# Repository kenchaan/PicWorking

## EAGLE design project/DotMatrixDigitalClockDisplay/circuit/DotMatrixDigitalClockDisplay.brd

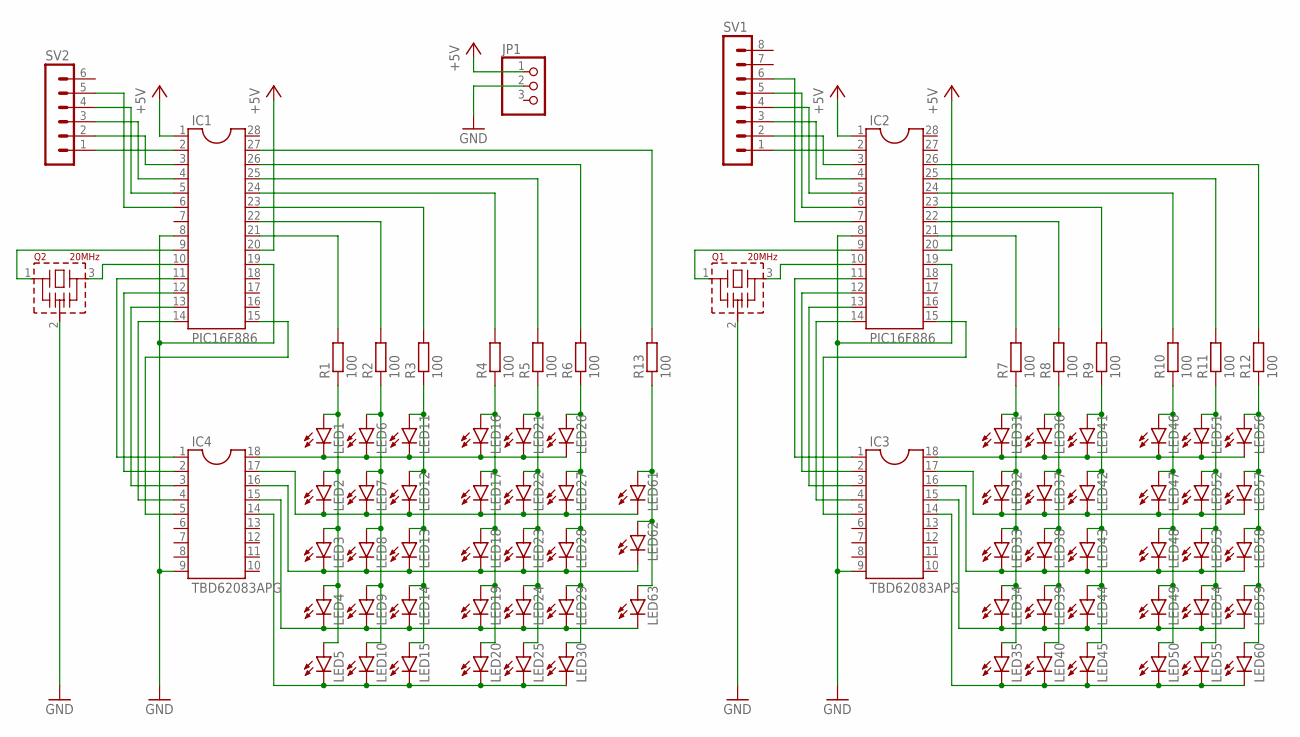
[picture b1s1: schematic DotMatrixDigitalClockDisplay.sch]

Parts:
IC1, IC2: PIC16F886; DIL28-3
IC3, IC4: TBD62083APG; DIL18
JP1: PINHD-1X3; 1X03
LED1, LED2, LED3, LED4, LED5, LED6, LED7, LED8, LED9, LED10, LED11, LED12, LED13, LED14, LED15, LED16, LED17, LED18, LED19, LED20, LED21, LED22, LED23, LED24, LED25, LED26, LED27, LED28, LED29, LED30, LED31, LED32, LED33, LED34, LED35, LED36, LED37, LED38, LED39, LED40, LED41, LED42, LED43, LED44, LED45, LED46, LED47, LED48, LED49, LED50, LED51, LED52, LED53, LED54, LED55, LED56, LED57, LED58, LED59, LED60, LED61, LED62, LED63: LED5MM
Q1, Q2: 20MHz; CSTLS_X
R1, R2, R3, R4, R5, R6, R7, R8, R9, R10, R11, R12, R13: 100; 0207/7
SV1: MA08-1
SV2: MA06-1

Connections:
+5V: IC1.1, IC1.20, IC2.1, IC2.20, JP1.1
GND: IC1.8, IC1.19, IC2.8, IC2.19, IC3.9, IC4.9, JP1.2, Q1.2 (VSS), Q2.2 (VSS)
unnamed: LED1.A, LED2.A, LED3.A, LED4.A, LED5.A, R1.1
unnamed: LED6.A, LED7.A, LED8.A, LED9.A, LED10.A, R2.1
unnamed: LED11.A, LED12.A, LED13.A, LED14.A, LED15.A, R3.1
unnamed: LED16.A, LED17.A, LED18.A, LED19.A, LED20.A, R4.1
unnamed: LED21.A, LED22.A, LED23.A, LED24.A, LED25.A, R5.1
unnamed: LED26.A, LED27.A, LED28.A, LED29.A, LED30.A, R6.1
unnamed: LED31.A, LED32.A, LED33.A, LED34.A, LED35.A, R7.1
unnamed: LED36.A, LED37.A, LED38.A, LED39.A, LED40.A, R8.1
unnamed: LED41.A, LED42.A, LED43.A, LED44.A, LED45.A, R9.1
unnamed: LED46.A, LED47.A, LED48.A, LED49.A, LED50.A, R10.1
unnamed: LED51.A, LED52.A, LED53.A, LED54.A, LED55.A, R11.1
unnamed: LED56.A, LED57.A, LED58.A, LED59.A, LED60.A, R12.1
unnamed: LED61.A, LED62.A, LED63.A, R13.1
unnamed: IC4.18, LED1.K (C), LED6.K (C), LED11.K (C), LED16.K (C), LED21.K (C), LED26.K (C)
unnamed: IC4.17, LED2.K (C), LED7.K (C), LED12.K (C), LED17.K (C), LED22.K (C), LED27.K (C), LED61.K (C)
unnamed: IC4.16, LED3.K (C), LED8.K (C), LED13.K (C), LED18.K (C), LED23.K (C), LED28.K (C), LED62.K (C)
unnamed: IC4.15, LED4.K (C), LED9.K (C), LED14.K (C), LED19.K (C), LED24.K (C), LED29.K (C), LED63.K (C)
unnamed: IC4.14, LED5.K (C), LED10.K (C), LED15.K (C), LED20.K (C), LED25.K (C), LED30.K (C)
unnamed: IC3.18, LED31.K (C), LED36.K (C), LED41.K (C), LED46.K (C), LED51.K (C), LED56.K (C)
unnamed: IC3.17, LED32.K (C), LED37.K (C), LED42.K (C), LED47.K (C), LED52.K (C), LED57.K (C)
unnamed: IC3.16, LED33.K (C), LED38.K (C), LED43.K (C), LED48.K (C), LED53.K (C), LED58.K (C)
unnamed: IC3.15, LED34.K (C), LED39.K (C), LED44.K (C), LED49.K (C), LED54.K (C), LED59.K (C)
unnamed: IC3.14, LED35.K (C), LED40.K (C), LED45.K (C), LED50.K (C), LED55.K (C), LED60.K (C)
unnamed: IC2.14, IC3.4
unnamed: IC2.13, IC3.3
unnamed: IC2.12, IC3.2
unnamed: IC2.11, IC3.1
unnamed: IC2.9, Q1.1
unnamed: IC2.21, R7.2
unnamed: IC2.22, R8.2
unnamed: IC2.23, R9.2
unnamed: IC2.24, R10.2
unnamed: IC2.25, R11.2
unnamed: IC2.26, R12.2
unnamed: IC2.10, Q1.3
unnamed: IC2.15, IC3.5
unnamed: IC1.14, IC4.4
unnamed: IC1.15, IC4.5
unnamed: IC1.13, IC4.3
unnamed: IC1.12, IC4.2
unnamed: IC1.11, IC4.1
unnamed: IC1.21, R1.2
unnamed: IC1.22, R2.2
unnamed: IC1.23, R3.2
unnamed: IC1.24, R4.2
unnamed: IC1.25, R5.2
unnamed: IC1.26, R6.2
unnamed: IC1.27, R13.2
unnamed: IC1.10, Q2.3
unnamed: IC1.9, Q2.1
unnamed: IC1.2, SV2.1
unnamed: IC1.3, SV2.2
unnamed: IC1.4, SV2.3
unnamed: IC1.5, SV2.4
unnamed: IC1.6, SV2.5
unnamed: IC2.2, SV1.1
unnamed: IC2.3, SV1.2
unnamed: IC2.4, SV1.3
unnamed: IC2.5, SV1.4
unnamed: IC2.6, SV1.5
unnamed: IC2.7, SV1.6

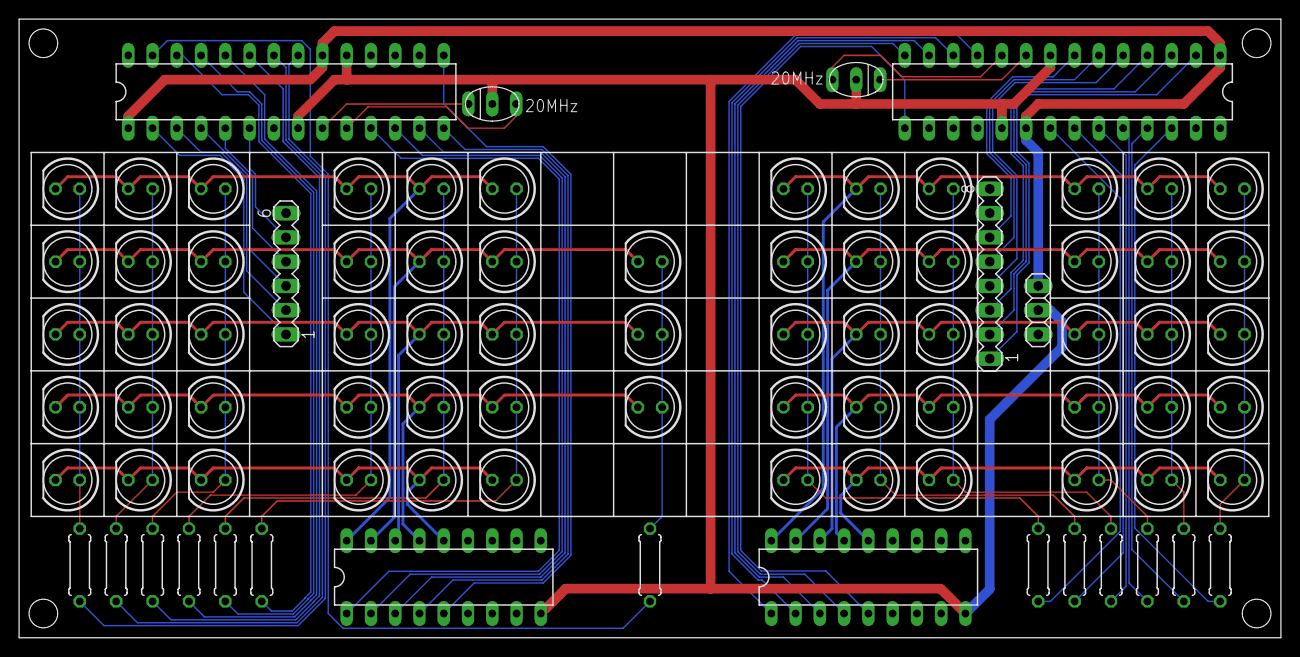
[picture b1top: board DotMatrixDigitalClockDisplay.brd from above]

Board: 2 copper layers, 132.1 x 64.8 mm, 85 parts (0 on the bottom side), 63 nets.

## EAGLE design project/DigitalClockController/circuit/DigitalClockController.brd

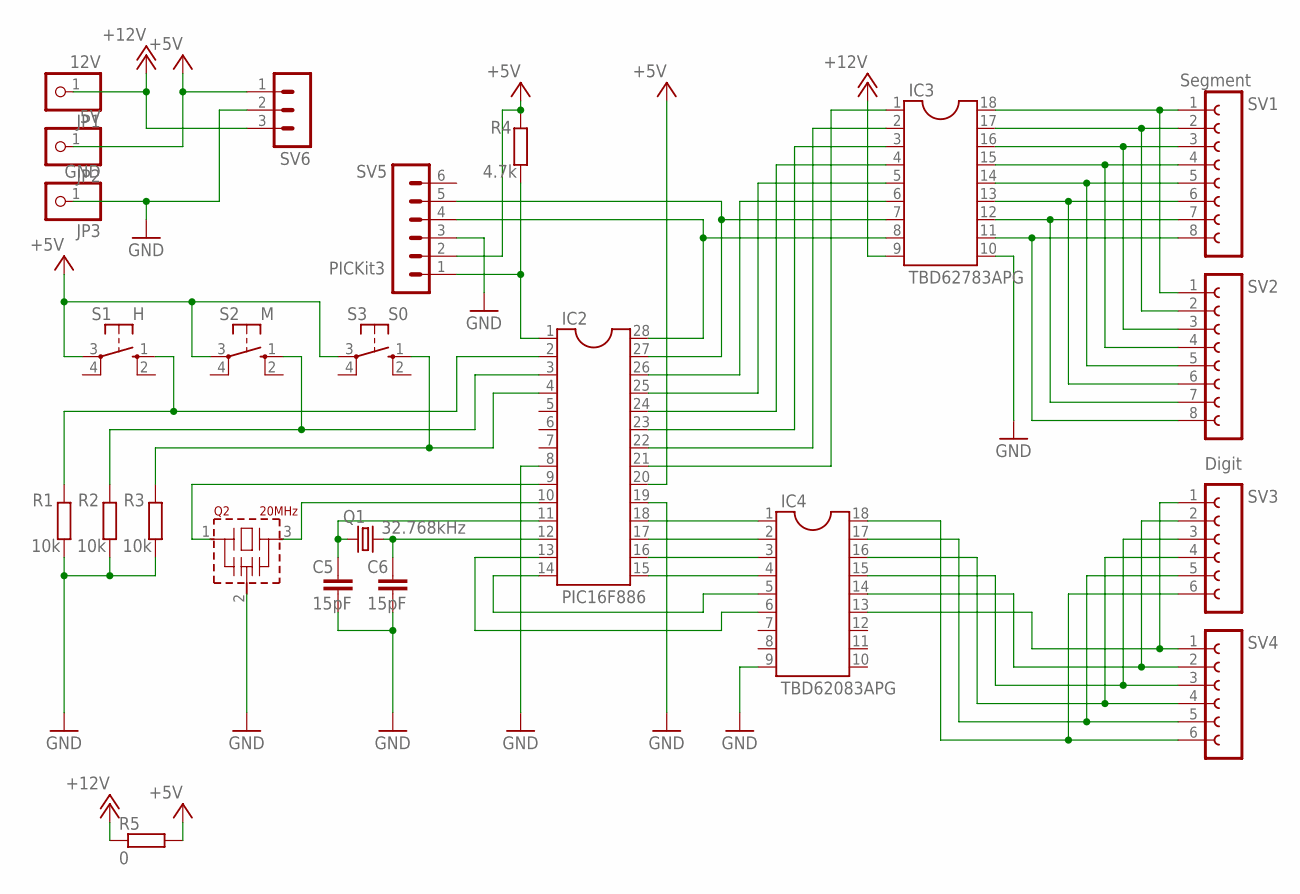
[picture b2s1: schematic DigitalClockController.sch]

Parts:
C5, C6: 15pF; C025-024X044
IC2: PIC16F886; DIL28-3
IC3: TBD62783APG; DIL18
IC4: TBD62083APG; DIL18
JP1: 12V; 1X01
JP2: 5V; 1X01
JP3: GND; 1X01
Q1: 32.768kHz; TC26H
Q2: 20MHz; CSTLS_X
R1, R2, R3: 10k; 0207/10
R4: 4.7k; 0207/10
R5: 0; 0207/10
S1: H; B3F-10XX
S2: M; B3F-10XX
S3: S0; B3F-10XX
SV1, SV2: Segment; FE08
SV3, SV4: Digit; FE06
SV5: PICKit3; MA06-1
SV6: MA03-1

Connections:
+5V: IC2.20, JP2.1, R4.2, R5.2, S1.3, S2.3, S3.3, SV5.2, SV6.1
+12V: IC3.9, JP1.1, R5.1, SV6.3
GND: C5.2, C6.2, IC2.8, IC2.19, IC3.10, IC4.9, JP3.1, Q2.2 (VSS), R1.1, R2.1, R3.1, SV5.3, SV6.2
unnamed: C5.1, IC2.11, Q1.2
unnamed: C6.1, IC2.12, Q1.1
unnamed: IC2.10, Q2.3
unnamed: IC2.9, Q2.1
unnamed: IC2.2, R1.2, S1.1 (S)
unnamed: IC2.3, R2.2, S2.1 (S)
unnamed: IC2.4, R3.2, S3.1 (S)
unnamed: IC2.1, R4.1, SV5.1
unnamed: IC3.18, SV1.1, SV2.1
unnamed: IC3.17, SV1.2, SV2.2
unnamed: IC3.16, SV1.3, SV2.3
unnamed: IC3.15, SV1.4, SV2.4
unnamed: IC2.26, IC3.6
unnamed: IC2.27, IC3.7, SV5.5
unnamed: IC2.25, IC3.5
unnamed: IC2.14, IC4.5
unnamed: IC2.13, IC4.6
unnamed: IC2.15, IC4.4
unnamed: IC2.18, IC4.1
unnamed: IC2.17, IC4.2
unnamed: IC2.16, IC4.3
unnamed: IC2.24, IC3.4
unnamed: IC2.23, IC3.3
unnamed: IC2.22, IC3.2
unnamed: IC2.21, IC3.1
unnamed: IC3.14, SV1.5, SV2.5
unnamed: IC3.13, SV1.6, SV2.6
unnamed: IC3.12, SV1.7, SV2.7
unnamed: IC3.11, SV1.8, SV2.8
unnamed: IC4.13, SV3.1, SV4.1
unnamed: IC4.14, SV3.2, SV4.2
unnamed: IC4.15, SV3.3, SV4.3
unnamed: IC4.16, SV3.4, SV4.4
unnamed: IC4.17, SV3.5, SV4.5
unnamed: IC4.18, SV3.6, SV4.6
unnamed: IC2.28, IC3.8, SV5.4

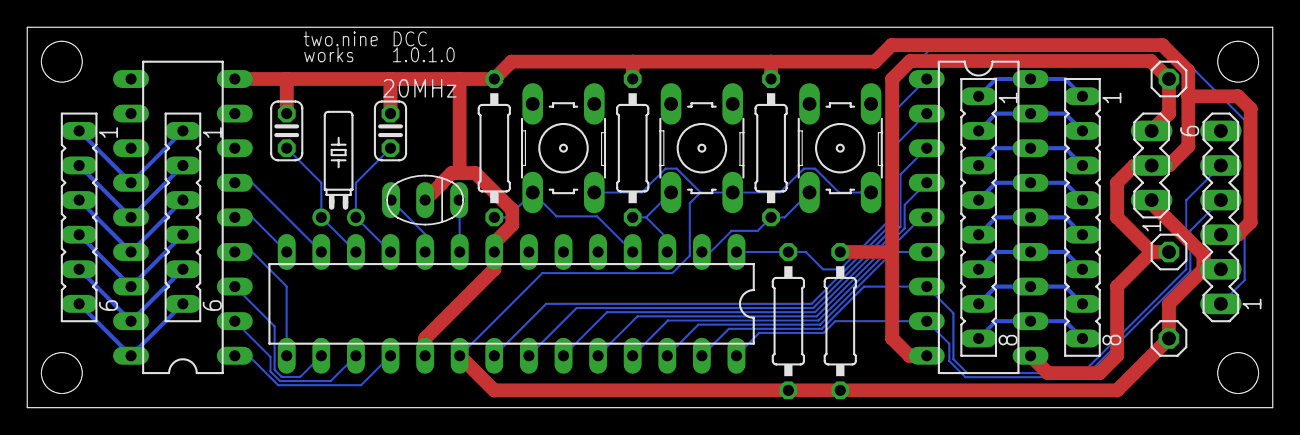
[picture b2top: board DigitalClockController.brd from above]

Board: 2 copper layers, 91.4 x 27.9 mm, 24 parts (0 on the bottom side), 39 nets.

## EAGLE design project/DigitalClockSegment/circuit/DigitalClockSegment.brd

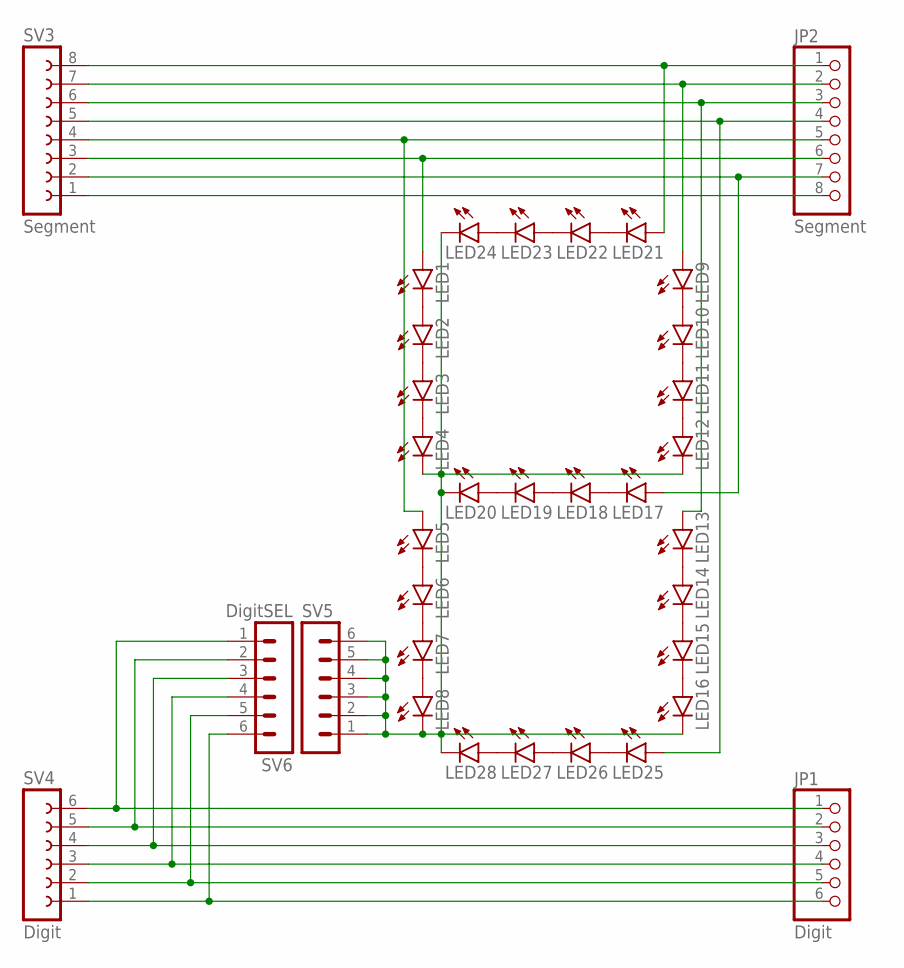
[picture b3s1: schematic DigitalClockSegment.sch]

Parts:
JP1: Digit; 1X06/90
JP2: Segment; 1X08/90
LED1, LED2, LED3, LED4, LED5, LED6, LED7, LED8, LED9, LED10, LED11, LED12, LED13, LED14, LED15, LED16, LED17, LED18, LED19, LED20, LED21, LED22, LED23, LED24, LED25, LED26, LED27, LED28: LED5MM
SV3: Segment; FE08W
SV4: Digit; FE06W
SV5: MA06-1
SV6: DigitSEL; MA06-1

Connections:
unnamed: LED1.K (C), LED2.A
unnamed: LED2.K (C), LED3.A
unnamed: LED3.K (C), LED4.A
unnamed: LED5.K (C), LED6.A
unnamed: LED6.K (C), LED7.A
unnamed: LED7.K (C), LED8.A
unnamed: LED9.K (C), LED10.A
unnamed: LED10.K (C), LED11.A
unnamed: LED11.K (C), LED12.A
unnamed: LED13.K (C), LED14.A
unnamed: LED14.K (C), LED15.A
unnamed: LED15.K (C), LED16.A
unnamed: LED17.K (C), LED18.A
unnamed: LED18.K (C), LED19.A
unnamed: LED19.K (C), LED20.A
unnamed: LED21.K (C), LED22.A
unnamed: LED22.K (C), LED23.A
unnamed: LED23.K (C), LED24.A
unnamed: LED25.K (C), LED26.A
unnamed: LED26.K (C), LED27.A
unnamed: LED27.K (C), LED28.A
unnamed: JP2.7, LED17.A, SV3.2
unnamed: JP1.1, SV4.6, SV6.1
unnamed: JP1.2, SV4.5, SV6.2
unnamed: JP1.3, SV4.4, SV6.3
unnamed: JP1.4, SV4.3, SV6.4
unnamed: JP1.5, SV4.2, SV6.5
unnamed: JP1.6, SV4.1, SV6.6
unnamed: JP2.1, LED21.A, SV3.8
unnamed: JP2.2, LED9.A, SV3.7
unnamed: JP2.3, LED13.A, SV3.6
unnamed: JP2.4, LED25.A, SV3.5
unnamed: JP2.5, LED5.A, SV3.4
unnamed: JP2.6, LED1.A, SV3.3
unnamed: LED4.K (C), LED8.K (C), LED12.K (C), LED16.K (C), LED20.K (C), LED24.K (C), LED28.K (C), SV5.1, SV5.2, SV5.3, SV5.4, SV5.5, SV5.6
unnamed: JP2.8, SV3.1

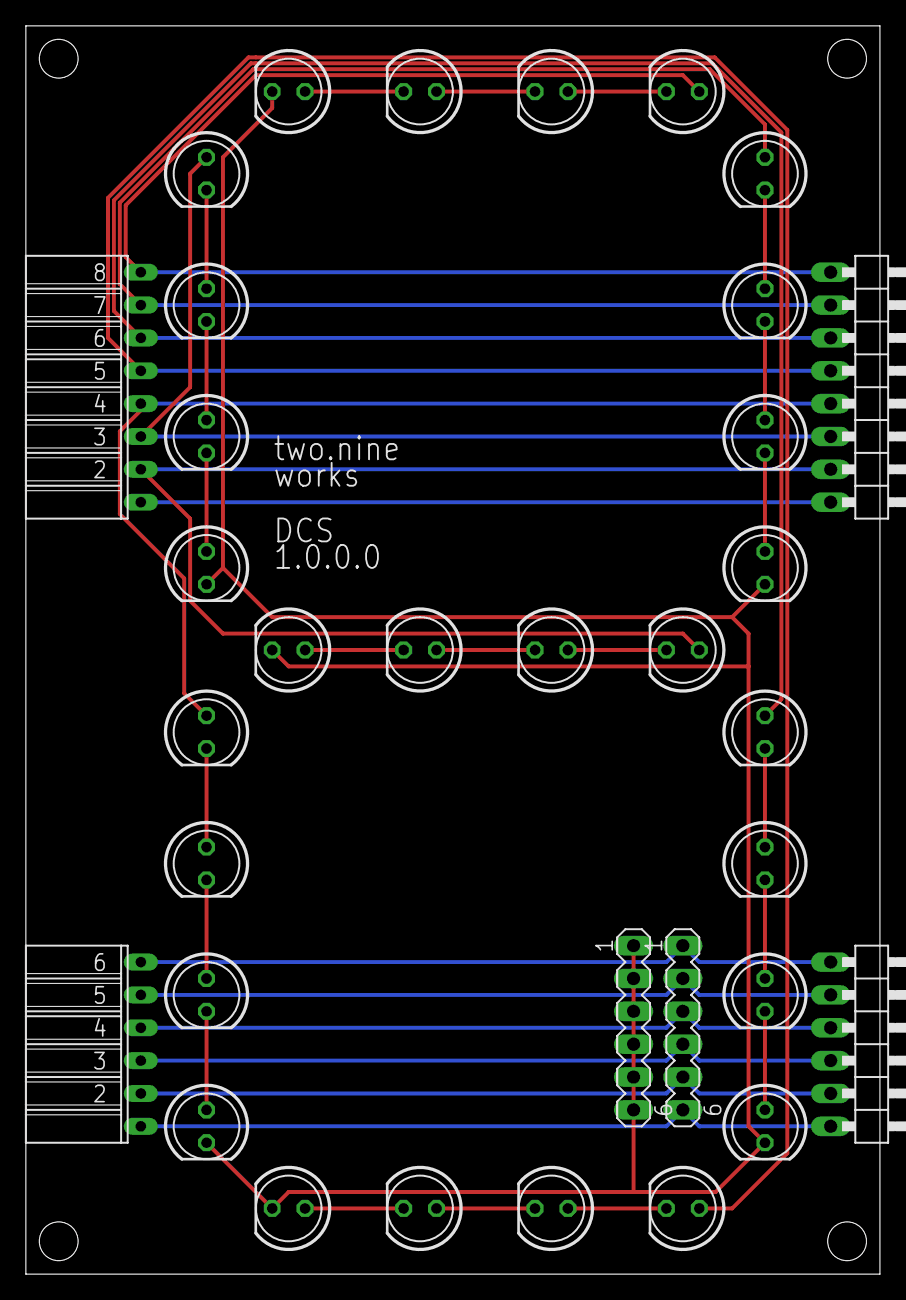
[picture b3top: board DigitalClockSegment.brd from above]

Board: 2 copper layers, 66.0 x 96.5 mm, 34 parts (0 on the bottom side), 36 nets.

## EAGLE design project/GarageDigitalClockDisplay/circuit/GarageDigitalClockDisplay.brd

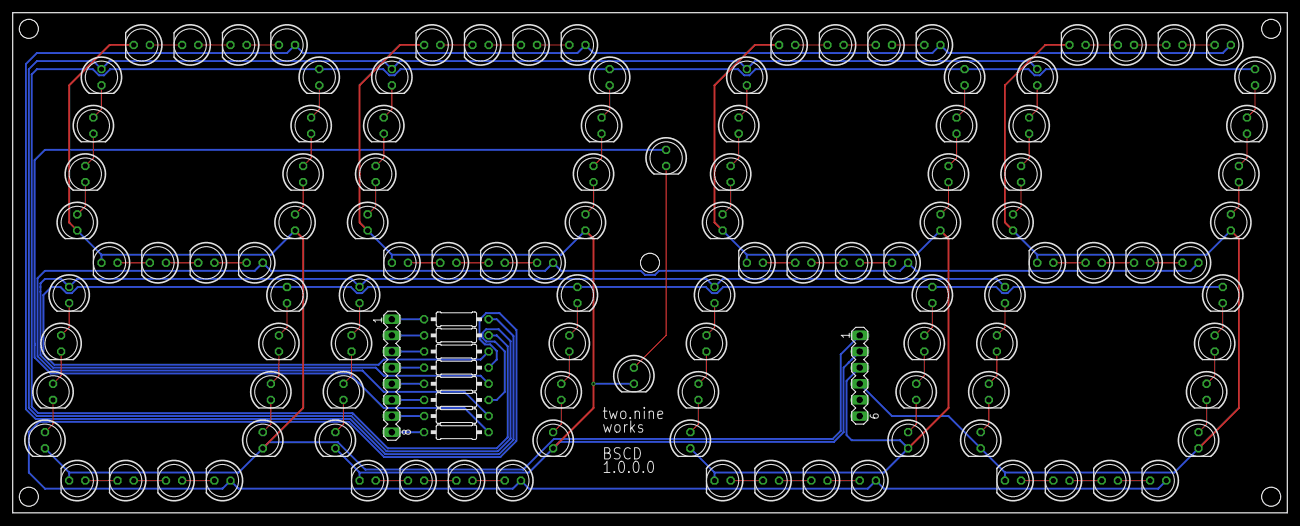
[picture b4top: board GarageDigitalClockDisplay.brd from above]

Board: 2 copper layers, 200.7 x 78.7 mm, 124 parts (0 on the bottom side), 105 nets.

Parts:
LED1, LED2, LED3, LED4, LED5, LED6, LED7, LED8, LED9, LED10, LED11, LED12, LED13, LED14, LED15, LED16, LED17, LED18, LED19, LED20, LED21, LED22, LED23, LED24, LED25, LED26, LED27, LED28, LED29, LED30, LED31, LED32, LED33, LED34, LED35, LED36, LED37, LED38, LED39, LED40, LED41, LED42, LED43, LED44, LED45, LED46, LED47, LED48, LED49, LED50, LED51, LED52, LED53, LED54, LED55, LED56, LED57, LED58, LED59, LED60, LED61, LED62, LED63, LED64, LED65, LED66, LED67, LED68, LED69, LED70, LED71, LED72, LED73, LED74, LED75, LED76, LED77, LED78, LED79, LED80, LED81, LED82, LED83, LED84, LED85, LED86, LED87, LED88, LED89, LED90, LED91, LED92, LED93, LED94, LED95, LED96, LED97, LED98, LED99, LED100, LED101, LED102, LED103, LED104, LED105, LED106, LED107, LED108, LED109, LED110, LED111, LED112, LED113, LED114: LED5MM
R1, R2, R3, R4, R5, R6, R7: 120; 0207/10
R8: 360; 0207/10
SV1: MA08-1
SV2: MA06-1

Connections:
unnamed: LED1.K, LED2.A
unnamed: LED2.K, LED3.A
unnamed: LED3.K, LED4.A
unnamed: LED5.K, LED6.A
unnamed: LED6.K, LED7.A
unnamed: LED7.K, LED8.A
unnamed: LED9.A, LED10.K
unnamed: LED10.A, LED11.K
unnamed: LED11.A, LED12.K
unnamed: LED13.A, LED14.K
unnamed: LED14.A, LED15.K
unnamed: LED15.A, LED16.K
unnamed: LED17.A, LED18.K
unnamed: LED18.A, LED19.K
unnamed: LED19.A, LED20.K
unnamed: LED21.K, LED22.A
unnamed: LED22.K, LED23.A
unnamed: LED23.K, LED24.A
unnamed: LED25.K, LED26.A
unnamed: LED26.K, LED27.A
unnamed: LED27.K, LED28.A
unnamed: R1.1, SV1.1
unnamed: LED1.A, LED29.A, LED59.A, LED87.A, R6.2
unnamed: LED5.A, LED33.A, LED63.A, LED91.A, R5.2
unnamed: LED20.A, LED48.A, LED78.A, LED106.A, R4.2
unnamed: R2.1, SV1.2
unnamed: LED21.A, LED49.A, LED79.A, LED107.A, R2.2
unnamed: R3.1, SV1.3
unnamed: LED4.K, LED8.K, LED9.K, LED13.K, LED17.K, LED24.K, LED28.K, SV2.1
unnamed: LED29.K, LED30.A
unnamed: LED30.K, LED31.A
unnamed: LED31.K, LED32.A
unnamed: LED33.K, LED34.A
unnamed: LED34.K, LED35.A
unnamed: LED35.K, LED36.A
unnamed: LED37.A, LED38.K
unnamed: LED38.A, LED39.K
unnamed: LED39.A, LED40.K
unnamed: LED41.A, LED42.K
unnamed: LED42.A, LED43.K
unnamed: LED43.A, LED44.K
unnamed: LED45.A, LED46.K
unnamed: LED46.A, LED47.K
unnamed: LED47.A, LED48.K
unnamed: LED49.K, LED50.A
unnamed: LED50.K, LED51.A
unnamed: LED51.K, LED52.A
unnamed: LED53.K, LED54.A
unnamed: LED54.K, LED55.A
unnamed: LED55.K, LED56.A
unnamed: R4.1, SV1.4
unnamed: R5.1, SV1.5
unnamed: R6.1, SV1.6
unnamed: R7.1, SV1.7
unnamed: R8.1, SV1.8
unnamed: LED32.K, LED36.K, LED37.K, LED41.K, LED45.K, LED52.K, LED56.K, LED58.K, SV2.2
unnamed: LED57.K, LED58.A
unnamed: LED57.A, R8.2
unnamed: LED59.K, LED60.A
unnamed: LED60.K, LED61.A
unnamed: LED61.K, LED62.A
unnamed: LED63.K, LED64.A
unnamed: LED64.K, LED65.A
unnamed: LED65.K, LED66.A
unnamed: LED67.A, LED68.K
unnamed: LED68.A, LED69.K
unnamed: LED69.A, LED70.K
unnamed: LED71.A, LED72.K
unnamed: LED72.A, LED73.K
unnamed: LED73.A, LED74.K
unnamed: LED75.A, LED76.K
unnamed: LED76.A, LED77.K
unnamed: LED77.A, LED78.K
unnamed: LED79.K, LED80.A
unnamed: LED80.K, LED81.A
unnamed: LED81.K, LED82.A
unnamed: LED83.K, LED84.A
unnamed: LED84.K, LED85.A
unnamed: LED85.K, LED86.A
unnamed: LED62.K, LED66.K, LED67.K, LED71.K, LED75.K, LED82.K, LED86.K, SV2.3
unnamed: LED87.K, LED88.A
unnamed: LED88.K, LED89.A
unnamed: LED89.K, LED90.A
unnamed: LED91.K, LED92.A
unnamed: LED92.K, LED93.A
unnamed: LED93.K, LED94.A
unnamed: LED95.A, LED96.K
unnamed: LED96.A, LED97.K
unnamed: LED97.A, LED98.K
unnamed: LED99.A, LED100.K
unnamed: LED100.A, LED101.K
unnamed: LED101.A, LED102.K
unnamed: LED103.A, LED104.K
unnamed: LED104.A, LED105.K
unnamed: LED105.A, LED106.K
unnamed: LED107.K, LED108.A
unnamed: LED108.K, LED109.A
unnamed: LED109.K, LED110.A
unnamed: LED111.K, LED112.A
unnamed: LED112.K, LED113.A
unnamed: LED113.K, LED114.A
unnamed: LED16.A, LED44.A, LED74.A, LED102.A, R7.2
unnamed: LED25.A, LED53.A, LED83.A, LED111.A, R3.2
unnamed: LED12.A, LED40.A, LED70.A, LED98.A, R1.2
unnamed: LED90.K, LED94.K, LED95.K, LED99.K, LED103.K, LED110.K, LED114.K, SV2.4

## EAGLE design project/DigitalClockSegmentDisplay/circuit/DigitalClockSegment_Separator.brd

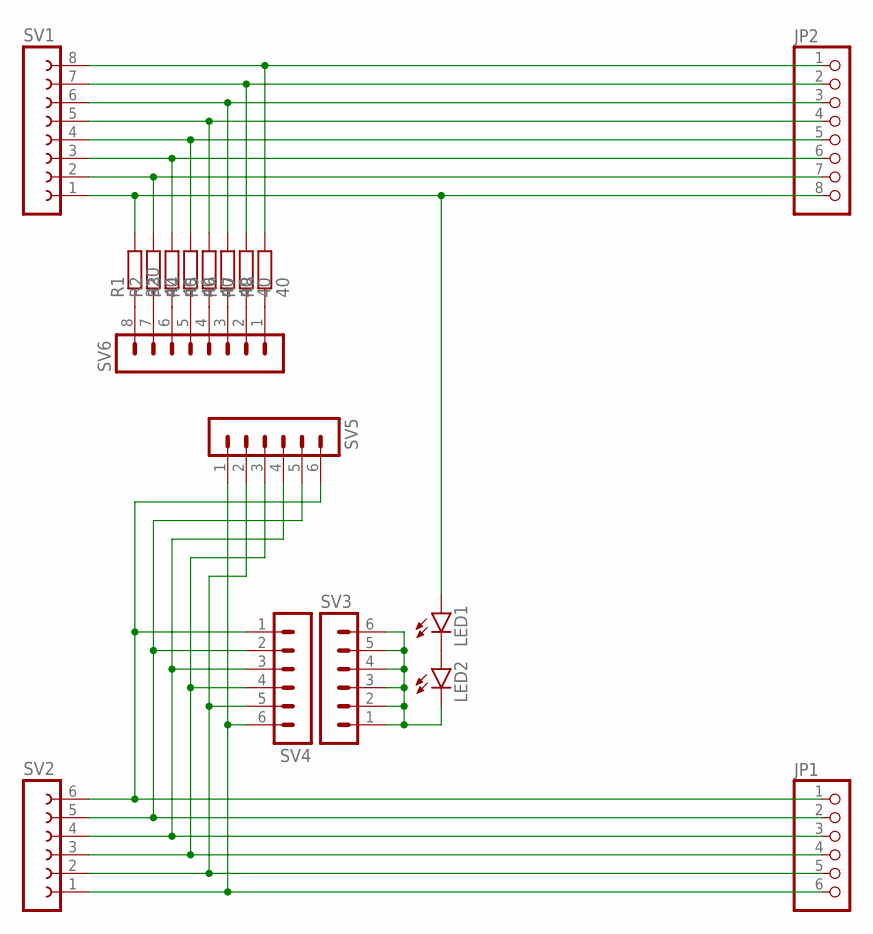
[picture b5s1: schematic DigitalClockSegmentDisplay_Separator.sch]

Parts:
JP1: PINHD-1X6/90; 1X06/90
JP2: PINHD-1X8/90; 1X08/90
LED1, LED2: LED5MM
R1: 320; 0207/10
R2, R3, R4, R5, R6, R7, R8: 40; 0207/10
SV1: FE08W
SV2: FE06W
SV3, SV4, SV5: MA06-1
SV6: MA08-1

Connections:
unnamed: JP2.1, R8.2, SV1.8
unnamed: JP2.2, R7.2, SV1.7
unnamed: JP2.3, R6.2, SV1.6
unnamed: JP2.4, R5.2, SV1.5
unnamed: JP2.5, R4.2, SV1.4
unnamed: JP2.6, R3.2, SV1.3
unnamed: JP2.7, R2.2, SV1.2
unnamed: JP2.8, LED1.A, R1.2, SV1.1
unnamed: JP1.1, SV2.6, SV4.1, SV5.6
unnamed: JP1.2, SV2.5, SV4.2, SV5.5
unnamed: JP1.3, SV2.4, SV4.3, SV5.4
unnamed: JP1.4, SV2.3, SV4.4, SV5.3
unnamed: JP1.5, SV2.2, SV4.5, SV5.2
unnamed: JP1.6, SV2.1, SV4.6, SV5.1
unnamed: LED2.K (C), SV3.1, SV3.2, SV3.3, SV3.4, SV3.5, SV3.6
unnamed: LED1.K (C), LED2.A
unnamed: R1.1, SV6.8
unnamed: R2.1, SV6.7
unnamed: R3.1, SV6.6
unnamed: R4.1, SV6.5
unnamed: R5.1, SV6.4
unnamed: R6.1, SV6.3
unnamed: R7.1, SV6.2
unnamed: R8.1, SV6.1

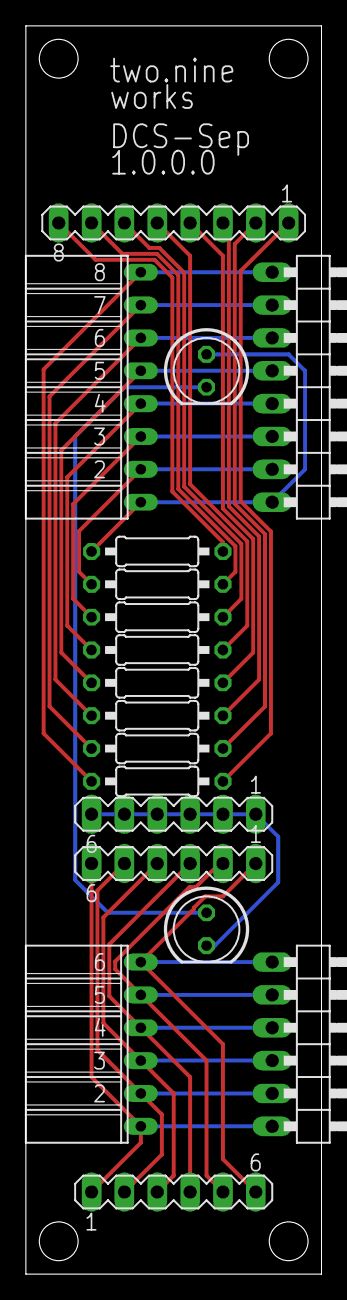
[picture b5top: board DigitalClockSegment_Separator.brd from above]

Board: 2 copper layers, 22.9 x 96.5 mm, 18 parts (0 on the bottom side), 24 nets.

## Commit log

2019-01-17 READMEファイルを追加
2019-01-17 初期ファイルを追加
2019-01-17 ツールを追加
2019-01-17 一旦ソフト部分完成
2019-01-17 テンプレートを更新
2019-01-19 DevBoardの回路・配線図を作成
2019-01-20 作ってみて回路を少し修正
2019-01-22 検証用のプログラムを作成
2019-01-23 TBD62083の使い方を修正
2019-01-23 入力チェック用のプログラムを作成
2019-01-23 回路図を作成
2019-01-23 最低限のプログラムを追加
2019-01-23 DevBoardでのソフト動作確認OK
2019-01-24 ボタン長押し時の間隔を変更
2019-01-24 コロンの点滅処理を作成
2019-01-25 割り込み処理を単純化
2019-01-25 PROC_FAILポートを変更
2019-01-25 分の設定で時が変わらないように修正
2019-01-25 コロンを7セグデータに変更
2019-01-29 プロジェクトを作成
    動きそうなコードも実装
2019-01-29 状態表示とPOWER制御を追加
2019-01-29 スイッチが押されたときのみカウントを更新するよう修正
2019-01-29 動きそうなコードを実装
2019-01-29 表示処理をPreProcessに変更
2019-01-29 EEPROMアクセス処理を追加
2019-01-29 不要なプロトタイプ宣言を削除
2019-02-12 テンプレートを変更
2019-02-15 EEPROM書き込み処理を修正
2019-02-15 設定温度を下げる処理を追加
2019-07-30 sakuraの設定ファイルを追加
2019-09-09 動きそうなプログラムを作成、時間設定はまだ
2019-09-10 秒のSWを削除
2019-09-10 スイッチ処理を作製
2019-09-10 時間表示更新のタイミングを0桁目と同時になるように変更
2019-09-10 長針の表示を修正
2019-09-10 変数名を変更
2019-09-10 全点灯確認処理を追加
2020-01-13 回路を作成
2020-01-13 アプリケーション以外を実装
2020-01-13 できたけどなんか点滅がおかしい
2020-01-14 これで割とちゃんと動くはず。
2020-01-14 WDTを追加
2020-01-14 プロジェクトファイルを追加
2020-01-14 動かしてみて修正
2020-01-14 回路を修正
2020-01-16 とりあえずWinkerFaderからソースを拝借
2020-01-16 PWM監視用のLEDを追加
2020-01-16 定義名を変更
2020-01-16 PORT,TMR,WDTを更新
2020-01-16 不要な定義を削除
2020-01-17 アプリケーション以外を作成
2020-01-17 ポジション機能用にポート設定を変更
2020-01-17 ポジションの出力処理を追加
2020-01-17 文字化けを修正
2020-01-17 不要な変更をもとに戻す
2020-01-17 ピン配置のコメントを修正
2020-01-17 回路をポジション付きに変更
2020-01-18 実装に合わせて回路を変更
2020-01-18 プロジェクト名を変更
2020-05-11 回路図・基板図を作成
2020-05-12 部品を追加
2020-05-12 ロゴを修正
2020-05-12 回路と配線を作成
2020-05-13 ガーバーデータを作成
2020-05-13 プログラムを作成
2020-05-13 PROCFAILを追加
2020-05-13 割り込みでメイン処理を実施
2020-05-13 プロジェクトを更新
2020-05-19 やっぱり割り込みでメイン処理をやめる
2020-05-19 処理を簡略化してみたつもり
2020-05-19 たぶんエラーになるのを修正
2020-05-20 セグメント出力をHW層に移動
2020-05-21 SimpleClockのプロジェクト設定を変更
2020-05-21 フォルダ名を変更
    DigitalClockSegment -> DigitalClockSegmentDisplay
2020-05-21 ファイル名を変更
    DigitalClockSegment -> DigitalClockSegmentDisplay
2020-05-26 GarageDigitalClockDisplayの回路と基板を作成
2020-06-03 レイアウトに自由度が出るようにDisplay接続端子を増やす
2020-06-04 ピン配置修正、5V-12V共通ジャンパ追加
2020-06-04 コントローラのピッチを変更
2020-06-04 フォルダ名を変更
2020-06-04 ファイル名を変更
2020-06-04 ファイルを追加
2020-06-04 DotMatrixDigitalClockDisplayの回路図を作成
2020-06-07 回路作成中
2020-06-10 DotMatrixDigitalClockDisplayの回路を作成
